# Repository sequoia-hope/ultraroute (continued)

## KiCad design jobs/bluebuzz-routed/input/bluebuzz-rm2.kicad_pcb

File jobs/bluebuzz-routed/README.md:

# bluebuzz-routed

bluebuzz fully routed by the MIT core router: **0 unconnected, 0 errors, no dangling copper** by
KiCad 9's DRC after a zone refill, under the board's own project rules (which make dangling
copper an error). Both USB pairs are routed as length-matched differential pairs (0.15 mm
tracks, 0.15 mm gap): USB_DP/USB_DM from the connector to the series resistors run side by side
for 76% and 72% of their length, 0.00 mm apart end to end (the hand-routed board: 31% side by
side); USB_DP_C/USB_DM_C, the 3.7 mm on from the resistors to the RP2350, run side by side on
F.Cu with no via for 58% and 60%, 0.13 mm apart (their pins are left out of the fan-out so the
pair reaches them straight). Stripped of all copper (the bluebuzz-kicad job), routed with
--strip-all --negotiate --rip-up --nudge --tighten --prefanout --diff-pairs --seed 2, 240 s on 1 thread (105.2 s used). No part moved. 265 vias and 1358
mm of track; the hand-finished board has 331 vias.

Command, on `jobs/bluebuzz-kicad/input/bluebuzz-rm2.kicad_pcb`:

    ultraroute route bluebuzz-rm2.kicad_pcb -o out.kicad_pcb --strip-all --negotiate --rip-up --nudge --tighten --prefanout --diff-pairs --seed 2 --timeout 240 --threads 1

The input here is that output after `tools/refill_zones.py`, so the pours show as KiCad fills
them. It is a finished board to look at, not a routing job: the studio loads it as it is. Lab
record: experiment `diffpairs-26`, run `BS-s2`; coupling and skew measured with
`cargo run --release -p grid --example pair_check`; see `docs/focus-trapped-escapes.md`.

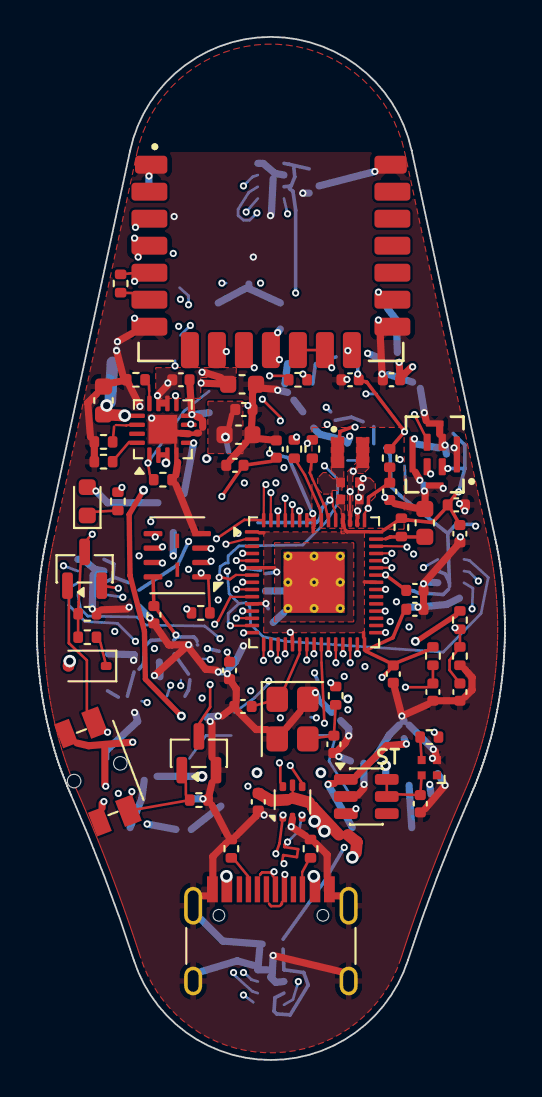
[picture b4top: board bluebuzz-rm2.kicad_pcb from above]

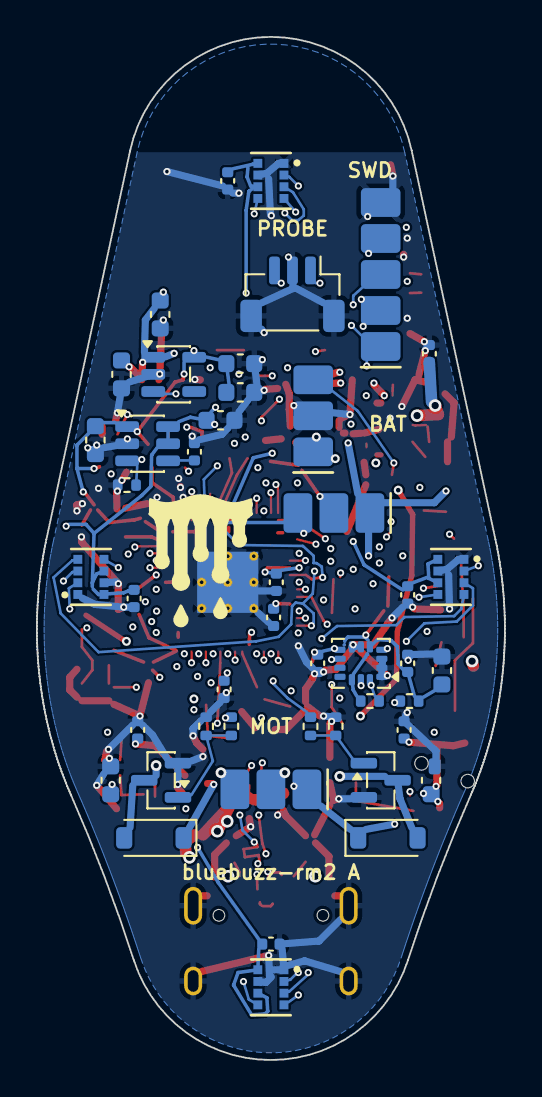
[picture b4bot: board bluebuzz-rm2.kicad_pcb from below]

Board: 6 copper layers, 26.0 x 56.8 mm, 109 parts (45 on the bottom side), 72 nets.

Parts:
C2, C13, C14, C15, C41, C43, C64, C82, C88, C89, C91, C92, C93, C94, C95, C96, C97, C98, C101, C102, C120, C121, C122, C123, C130, C132, C133, C140: 100n; C_0402_1005Metric
C10, C11, C12, C22, C52, C100, C131: 10u; C_0603_1608Metric
C20, C21, C51, C85: 1u; C_0603_1608Metric
C40, C42: 22u; C_0603_1608Metric
C50: 470p; C_0402_1005Metric
C80, C83: 4.7u; C_0402_1005Metric_small_pads
C81, C84: 4.7u; C_0402_1005Metric
C86, C87: 15p; C_0402_1005Metric
D1: CHG; LED_0603_1608Metric
D2: XL-1010RGBC; LED_1010_WS2812
D3, D4: B5819W; D_SOD-123
D5: BAT54C; SOT-23
D6: 1N4148WS; D_SOD-323
J1: USB-C; USB_C_Receptacle_HRO_TYPE-C-31-M-12
J2: BAT; PadRow_3x_solder
J3: SWD; PadRow_5x_pogo
J4: MOT; PadRow_3x_solder
J5: TP; PadRow_3x_pogo
J6: PROBE; JST_SH_BM03B-SRSS-TB_1x03-1MP_P1.00mm_Vertical
L1: 3.3u; L_pol_2016
Q1, Q2: AO3400A; SOT-23
Q3: 2N7002; SOT-23
R1, R2: 5.1k; R_0402_1005Metric
R3, R4: 27R; R_0402_1005Metric
R10: 1.78k; R_0402_1005Metric
R11: 1.62k; R_0402_1005Metric
R12: 45.3k; R_0402_1005Metric
R13, R81, R88: 10k; R_0402_1005Metric
R14, R62: 330R; R_0402_1005Metric
R40, R42: 100R; R_0402_1005Metric
R41, R43, R130, R131: 4.7k; R_0402_1005Metric
R50, R63, R64, R66: 100k; R_0402_1005Metric
R60, R61: 1M; R_0402_1005Metric
R80: 470R; R_0402_1005Metric
R84: 33R; R_0402_1005Metric
R85: 10R; R_0402_1005Metric
R86, R87: 1k; R_0402_1005Metric
SW1: PWR; Panasonic_EVQPUL_EVQPUC
U1: RP2350A; QFN-60-1EP_7x7mm_P0.4mm_EP3.4x3.4mm_ThermalVias
U2: BQ24074RGT; VQFN-16-1EP_3x3mm_P0.5mm_EP1.6x1.6mm
U3: TLV75533PDBV; SOT-23-5
U5, U11: TPS22918DBVR; SOT-23-6
U6: W25Q32JVUUIQ; Winbond_USON-8-2EP_3x4mm_P0.8mm_EP0.2x0.8mm
U7: RM2
U10: USBLC6-2P6; SOT-666
U20, U21, U22, U23: DPS368; DPS368_LGA-8
U30: LSM6DS3TR-C; LGA-14_3x2.5mm_P0.5mm_LayoutBorder3x4y
U40: MP34DT05-A; MP34DT05_HCLGA-4
Y1: 12MHz; Crystal_SMD_3225-4Pin_3.2x2.5mm

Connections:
1V1: C80.1, C81.1, C82.1, C98.1, J5.3, L1.1, U1.6, U1.23, U1.39, U1.50
3V3A: C85.1, R85.2, U1.44
3V3_SENS: C52.1, C120.1, C121.1, C122.1, C123.1, U5.5, U5.6, U20.6, U20.8, U21.6, U21.8, U22.6, U22.8, U23.6, U23.8
3V3_SYS: C21.1, C22.1, C51.1, C83.1, C88.1, C91.1, C92.1, C93.1, C94.1, C95.1, C96.1, C97.1, C102.1, C130.1, C131.1, C132.1, C140.1, J5.2, R84.1, R85.1, R88.1, R130.1, R131.1, U1.1, U1.11, U1.20, U1.30, U1.38, U1.45, U1.49, U1.53, U1.54, U3.5, U5.1, U6.8, U7.14, U11.3, U30.5, U30.8, U30.12, U40.1
BOOTSEL: J3.4, R87.2
BTN: Q3.3, U1.12
BTN_RAW: D5.1, Q3.1, R64.1, SW1.2
CC1: J1.A5, R1.1
CC2: J1.B5, R2.1
CHG_LED: D1.1, R14.1
CHG_N: R14.2, U2.9
CT_SENS: C50.1, U5.4
GND: C2.2, C10.2, C11.2, C12.2, C13.2, C14.2, C15.2, C20.2, C21.2, C22.2, C40.2, C41.2, C42.2, C43.2, C50.2, C51.2, C52.2, C64.2, C80.2, C81.2, C82.2, C83.2, C84.2, C85.2, C86.2, C87.2, C88.2, C89.2, C91.2, C92.2, C93.2, C94.2, C95.2, C96.2, C97.2, C98.2, C100.2, C101.2, C102.2, C120.2, C121.2, C122.2, C123.2, C130.2, C131.2, C132.2, C133.2, C140.2, D2.3, J1.A1, J1.A12, J1.B1, J1.B12, J1.S1, J2.2, J3.5, J6.2, J6.MP, Q1.2, Q2.2, Q3.2, R1.2, R2.2, R10.2, R11.2, R12.2, R13.2, R41.2, R43.2, R50.2, R61.2, R63.2, R64.2, U1.47, U1.61, U2.4, U2.6, U2.8, U2.17, U3.2, U5.2, U6.4, U7.1, U7.4, U7.7, U7.11, U7.15, U7.21, U10.2, U11.2, U20.1, U20.7, U21.1, U21.7, U22.1, U22.7, U23.1, U23.7, U30.1, U30.2, U30.3, U30.6, U30.7, U40.2, U40.5, Y1.2, Y1.4
ILIM: R11.1, U2.12
IMU_INT1: U1.8, U30.4
IMU_INT2: U1.29, U30.9
ISET: R10.1, U2.16
LDO_EN: D5.3, R63.1, R66.2, U3.3
LED_DIN: D2.4, R62.2
LED_STAT: R62.1, U1.34
LED_VDD: C133.1, D2.2, U11.5, U11.6
MOTOR1_G: Q1.1, R40.2, R41.1
MOTOR1_PWM: R40.1, U1.17
MOTOR1_SW: D3.2, J4.2, Q1.3
MOTOR2_G: Q2.1, R42.2, R43.1
MOTOR2_PWM: R42.1, U1.28
MOTOR2_SW: D4.2, J4.3, Q2.3
PDM_CLK: U1.43, U40.3
PDM_DATA: U1.42, U40.4
PG_N: U1.13, U2.7
PWR_HOLD: D5.2, U1.31
QSPI_SCLK: U1.56, U6.6
QSPI_SD0: U1.57, U6.5
QSPI_SD1: U1.59, U6.2
QSPI_SD2: U1.58, U6.3
QSPI_SD3: U1.55, U6.7
QSPI_SS: R87.1, U1.60, U6.1
RUN: C89.1, J3.3, R88.2, U1.26
SCL: R131.2, U1.10, U30.13
SDA: R130.2, U1.9, U30.14
SENS_EN: R50.1, U1.7, U5.3
SWCLK: J3.2, J6.1, U1.24
SWDIO: J3.1, J6.3, U1.25
TAC_CS1: U1.2, U20.2
TAC_CS2: U1.18, U21.2
TAC_CS3: U1.19, U22.2
TAC_CS4: U1.27, U23.2
TAC_SCK: U1.14, U20.4, U21.4, U22.4, U23.4
TAC_SDI: U1.15, U20.3, U21.3, U22.3, U23.3
TAC_SDO: U1.16, U20.5, U21.5, U22.5, U23.5
TMR: R12.1, U2.14
TS: J2.3, R13.1, U2.1
USB_DM: J1.A7, J1.B7, R4.1, U10.3, U10.4
USB_DM_C: R4.2, U1.51
USB_DP: J1.A6, J1.B6, R3.1, U10.1, U10.6
USB_DP_C: R3.2, U1.52
VBAT: C12.1, C15.1, J2.1, R60.1, U2.2, U2.3
VBAT_SENSE: C64.1, R60.2, R61.1, U1.40
VBUS: C2.1, C10.1, C13.1, D6.2, J1.A4, J1.A9, J1.B4, J1.B9, U2.13, U10.5
VBUS_EN: D6.1, R66.1
VREG_AVDD: C84.1, R84.2, U1.46
VREG_LX: L1.2, U1.48
VSYS: C11.1, C14.1, C20.1, C40.1, C41.1, C42.1, C43.1, C100.1, C101.1, D1.2, D3.1, D4.1, J4.1, J5.1, SW1.1, U2.5, U2.10, U2.11, U3.1, U7.16, U11.1
WL_CLK: U1.5, U7.3
WL_CS: U1.37, U7.9
WL_DATA: R80.2, R81.2, U1.4, U7.5
WL_DOUT: R80.1, U7.6
WL_IRQ: R81.1, U7.10
WL_ON: U1.41, U7.12, U7.13
XIN: C86.1, U1.21, Y1.1
XOUT: R86.1, U1.22
XTAL2: C87.1, R86.2, Y1.3

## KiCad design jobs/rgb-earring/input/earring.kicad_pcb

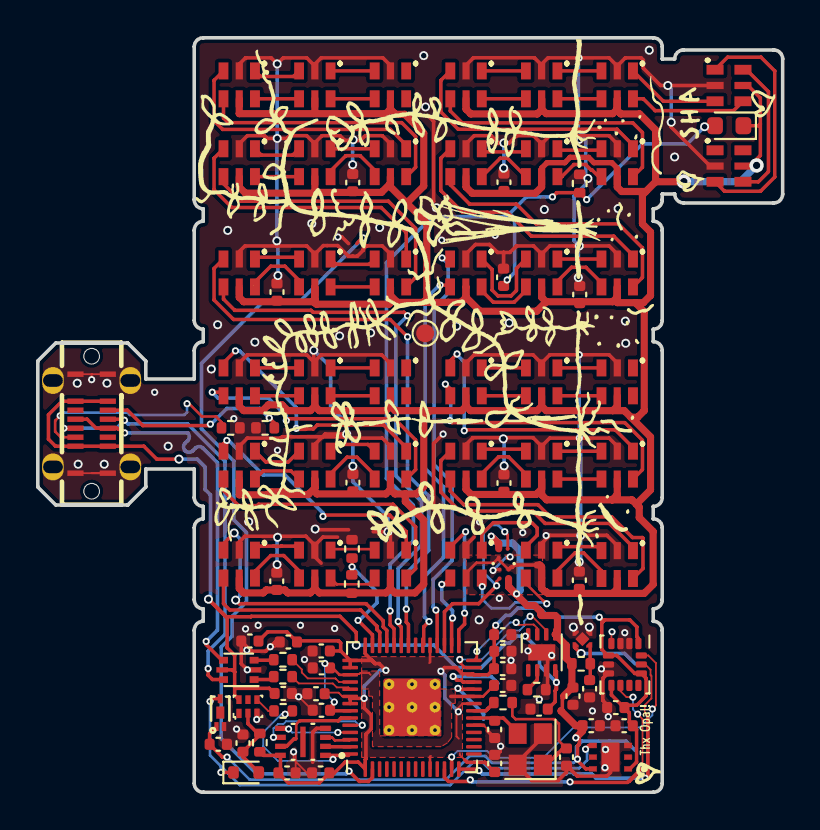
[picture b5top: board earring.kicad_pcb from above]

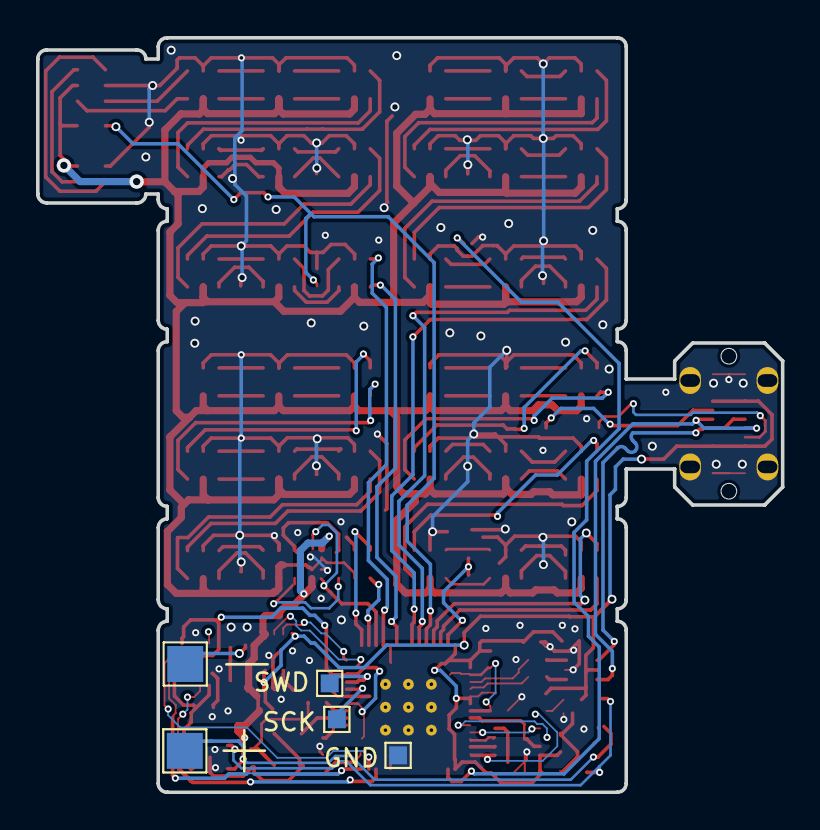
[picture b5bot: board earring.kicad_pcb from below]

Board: 2 copper layers, 41.4 x 41.9 mm, 104 parts (5 on the bottom side), 115 nets.

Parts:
C1, C4, C8, C9, C11, C13, C14, C15, C16, C17, C18, C19, C22, C23, C24: 100n; C_0402_1005Metric
C2, C3, C7, C21: 10u; C_0402_1005Metric
C5, C6: 20p; C_0402_1005Metric
C10, C12, C20, C25, C26, C27, C28, C29, C30, C31, C32, C33: 1u; C_0402_1005Metric
D2: D; D_SOD-523
J2: USB_C_Receptacle_USB2.0; USB-C-TH_GT-USB-7055
Q5: light_sensor; LED_0603_1608Metric
R1, R5: 1.1k; R_0402_1005Metric
R2, R12: 100k; R_0402_1005Metric
R3, R4, R8: 5.1k; R_0402_1005Metric
R6, R7: 27; R_0402_1005Metric
R9: 510; R_0402_1005Metric
R10: 10k; R_0402_1005Metric
R11: 40.2k; R_0402_1005Metric
TP1: TestPoint; TestPoint_Pad_D1.0mm
TP2, TP3: TestPoint; TestPoint_Pad_2.0x2.0mm
TP4, TP5, TP6: TestPoint; TestPoint_Pad_1.0x1.0mm
U1: Magnetic Switch; DFN1608-3_L1.5-W0.8-P0.42-BL-EP
U3: RP2040; RP2040-QFN-56
U4: W25Q16JVUXIQ; IC_W25Q16JVUXIQ_TR
U5, U11, U12, U13, U14, U15, U16, U17, U18, U19, U21, U22, U25, U26, U27, U28, U29, U30, U31, U32, U33, U34, U35, U36, U37, U38, U39, U40, U41, U42, U45, U46, U47, U48, U49, U50, U52: LED-SK9822-EC20
U6: Buffer; UFDFN-6_1.45x1mm
U7: LSM6DS3; LGA-14_3x2.5mm_P0.5mm_LayoutBorder3x4y
U8: DS6091AED4; DFN1x1
U9: NCP730BMT330TBG; WDFN-6-2x2
U10: USBLC6-2P6; SOT-666
U20: LGS4056H; DFN-8-1EP_2x2mm_P0.5mm_EP0.9x1.5mm
U24: SK9822-EC20; LED-SK9822-EC20
U43, U44: TPS22913BYZVR; YZV0004ADAD
Y1: Crystal_GND24; Crystal_SMD_2520-4Pin_2.5x2.0mm

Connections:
+1V1: C8.1, C9.1, C10.1, U3.23 (DVDD), U3.45 (VREG_VOUT), U3.50 (DVDD)
+3V3: C1.1, C7.1, C11.1, C12.1, C13.1, C14.1, C15.1, C16.1, C17.1, C18.1, C20.1, C23.1, R2.1, U3.1 (IOVDD), U3.10 (IOVDD), U3.22 (IOVDD), U3.26 (RUN), U3.33 (IOVDD), U3.42 (IOVDD), U3.43 (ADC_AVDD), U3.44 (VREG_IN), U3.48 (USB_VDD), U3.49 (IOVDD), U4.8 (VCC), U7.1 (SDO/SA0), U7.5 (VDDIO), U7.8 (VDD), U7.12 (CS), U9.1 (OUT)
+BATT: C2.1, C19.1, C21.1, R9.2, TP3.1, U1.1 (VCC), U9.6 (IN), U20.5 (BAT), U43.A2 (VIN), U44.A2 (VIN)
/3v3EN: D2.1 (K), U1.2 (VOUT), U9.4 (EN)
/BATT_SENSE: R11.1, R12.2, U3.41 (GPIO29_ADC3)
/CHRG: U3.27 (GPIO16), U20.6 (Done)
/DONE: U3.28 (GPIO17), U20.7 (CHRG)
/LED_1_V: C25.1, C26.1, C27.1, C28.1, C29.1, C30.1, C31.1, C32.1, Q5.1, R11.2, U5.5 (VDD), U11.5 (VDD), U12.5 (VDD), U13.5 (VDD), U14.5 (VDD), U15.5 (VDD), U16.5 (VDD), U17.5 (VDD), U18.5 (VDD), U19.5 (VDD), U21.5 (VDD), U22.5 (VDD), U24.5 (VDD), U25.5 (VDD), U26.5 (VDD), U27.5 (VDD), U28.5 (VDD), U29.5 (VDD), U30.5 (VDD), U31.5 (VDD), U32.5 (VDD), U33.5 (VDD), U34.5 (VDD), U35.5 (VDD), U36.5 (VDD), U37.5 (VDD), U38.5 (VDD), U39.5 (VDD), U40.5 (VDD), U41.5 (VDD), U42.5 (VDD), U43.A1 (VOUT), U44.A1 (VOUT), U45.5 (VDD), U46.5 (VDD), U47.5 (VDD), U48.5 (VDD), U49.5 (VDD), U50.5 (VDD), U52.5 (VDD)
/LED_SCK_1: U3.30 (GPIO19), U48.4 (CKL)
/LED_SCK_2: U3.34 (GPIO22), U41.4 (CKL)
/LED_SCK_3: U3.37 (GPIO25), U38.4 (CKL)
/LED_SCK_4: U3.40 (GPIO28_ADC2), U45.4 (CKL)
/LED_TX_1: U3.29 (GPIO18), U48.3 (SDI)
/LED_TX_2: U3.32 (GPIO21), U41.3 (SDI)
/LED_TX_3: U3.36 (GPIO24), U38.3 (SDI)
/LED_TX_4: U3.39 (GPIO27_ADC1), U45.3 (SDI)
/LIGHT_SENSE: C33.1, Q5.2, R8.1, U3.38 (GPIO26_ADC0)
/QSPI_SCLK: U3.52 (QSPI_SCLK), U4.6 (CLK)
/QSPI_SD0: U3.53 (QSPI_SD0), U4.5 (DI_(IO0))
/QSPI_SD1: U3.55 (QSPI_SD1), U4.2 (DO_(IO1))
/QSPI_SD2: U3.54 (QSPI_SD2), U4.3 (~WP_(IO2))
/QSPI_SD3: U3.51 (QSPI_SD3), U4.7 (~HOLD_(IO3))
/QSPI_SS: R1.1, U3.56 (QSPI_SS), U4.1 (~{CS)
/SW_LED_1: U3.31 (GPIO20), U43.B2 (ON), U44.B2 (ON)
/USB_D1+: R6.1, U10.1 (I/O1)
/USB_D1-: R7.1, U10.3 (I/O2)
/USB_D+: J2.A6 (D+), J2.B6 (D+), U10.6 (I/O1)
/USB_D-: J2.A7 (D-), J2.B7 (D-), U10.4 (I/O2)
/USB_DN: R7.2, U3.46 (USB_DM)
/USB_DP: R6.2, U3.47 (USB_DP)
/XIN: C5.1, U3.20 (XIN), Y1.3
/XOUT: R5.1, U3.21 (XOUT)
/~USB_BOOT: R1.2, U6.4
BAT-: TP2.1, U8.4 (EB-)
GND: C1.2, C2.2, C3.2, C4.2, C5.2, C6.2, C7.2, C8.2, C9.2, C10.2, C11.2, C12.2, C13.2, C14.2, C15.2, C16.2, C17.2, C18.2, C19.2, C20.2, C21.2, C22.2, C23.2, C24.2, C25.2, C26.2, C27.2, C28.2, C29.2, C30.2, C31.2, C32.2, C33.2, J2.A1 (GND), J2.A12 (GND), J2.B1 (GND), J2.B12 (GND), J2.S1 (SHIELD), R3.1, R4.2, R8.2, R10.1, R12.1, TP1.1, TP6.1, U1.3 (GND), U3.19 (TESTEN), U3.57 (GND), U4.4 (GND), U5.2 (GND), U6.3 (GND), U7.2 (SDX), U7.3 (SCX), U7.6 (GND), U7.7 (GND), U8.2 (VSS), U8.3 (VSS), U8.5 (VSS), U9.3 (GND), U9.EP (EPAD), U10.2 (GND), U11.2 (GND), U12.2 (GND), U13.2 (GND), U14.2 (GND), U15.2 (GND), U16.2 (GND), U17.2 (GND), U18.2 (GND), U19.2 (GND), U20.3 (GND), U20.9 (PAD), U21.2 (GND), U22.2 (GND), U24.2 (GND), U25.2 (GND), U26.2 (GND), U27.2 (GND), U28.2 (GND), U29.2 (GND), U30.2 (GND), U31.2 (GND), U32.2 (GND), U33.2 (GND), U34.2 (GND), U35.2 (GND), U36.2 (GND), U37.2 (GND), U38.2 (GND), U39.2 (GND), U40.2 (GND), U41.2 (GND), U42.2 (GND), U43.B1 (GND), U44.B1 (GND), U45.2 (GND), U46.2 (GND), U47.2 (GND), U48.2 (GND), U49.2 (GND), U50.2 (GND), U52.2 (GND), Y1.2, Y1.4
INT: U3.12 (GPIO9), U7.9 (INT2)
unnamed: C6.1, R5.2, Y1.1
unnamed: C3.1, D2.2 (A), R2.2, U6.2
unnamed: J2.A5 (CC1), R3.2
unnamed: J2.B5 (CC2), R4.1
unnamed: C22.1, R9.1, U8.1 (BAT)
unnamed: U5.6 (CKO), U11.4 (CKL)
unnamed: U11.6 (CKO), U12.4 (CKL)
unnamed: U5.1 (SDO), U11.3 (SDI)
unnamed: U11.1 (SDO), U12.3 (SDI)
unnamed: U13.4 (CKL), U47.6 (CKO)
unnamed: U13.6 (CKO), U14.4 (CKL)
unnamed: U13.3 (SDI), U47.1 (SDO)
unnamed: U13.1 (SDO), U14.3 (SDI)
unnamed: U14.6 (CKO), U15.4 (CKL)
unnamed: U14.1 (SDO), U15.3 (SDI)
unnamed: U5.4 (CKL), U15.6 (CKO)
unnamed: U5.3 (SDI), U15.1 (SDO)
unnamed: U16.4 (CKL), U22.6 (CKO)
unnamed: U16.6 (CKO), U17.4 (CKL)
unnamed: U16.3 (SDI), U22.1 (SDO)
unnamed: U16.1 (SDO), U17.3 (SDI)
unnamed: U17.6 (CKO), U18.4 (CKL)
unnamed: U17.1 (SDO), U18.3 (SDI)
unnamed: U19.4 (CKL), U52.6 (CKO)
unnamed: U19.6 (CKO), U21.4 (CKL)
unnamed: U19.3 (SDI), U52.1 (SDO)
unnamed: U19.1 (SDO), U21.3 (SDI)
unnamed: R10.2, U20.2 (Prog)
unnamed: U21.6 (CKO), U22.4 (CKL)
unnamed: U21.1 (SDO), U22.3 (SDI)
unnamed: U24.4 (CKL), U33.6 (CKO)
unnamed: U24.6 (CKO), U25.4 (CKL)
unnamed: U24.3 (SDI), U33.1 (SDO)
unnamed: U24.1 (SDO), U25.3 (SDI)
unnamed: U25.6 (CKO), U26.4 (CKL)
unnamed: U25.1 (SDO), U26.3 (SDI)
unnamed: U27.4 (CKL), U36.6 (CKO)
unnamed: U27.6 (CKO), U28.4 (CKL)
unnamed: U27.3 (SDI), U36.1 (SDO)
unnamed: U27.1 (SDO), U28.3 (SDI)
unnamed: U28.6 (CKO), U29.4 (CKL)
unnamed: U28.1 (SDO), U29.3 (SDI)
unnamed: U29.6 (CKO), U30.4 (CKL)
unnamed: U29.1 (SDO), U30.3 (SDI)
unnamed: U30.6 (CKO), U37.4 (CKL)
unnamed: U30.1 (SDO), U37.3 (SDI)
unnamed: U31.4 (CKL), U40.6 (CKO)
unnamed: U31.6 (CKO), U32.4 (CKL)
unnamed: U31.3 (SDI), U40.1 (SDO)
unnamed: U31.1 (SDO), U32.3 (SDI)
unnamed: U32.6 (CKO), U33.4 (CKL)
unnamed: U32.1 (SDO), U33.3 (SDI)
unnamed: U34.4 (CKL), U50.6 (CKO)
unnamed: U34.6 (CKO), U35.4 (CKL)
unnamed: U34.3 (SDI), U50.1 (SDO)
unnamed: U34.1 (SDO), U35.3 (SDI)
unnamed: U35.6 (CKO), U36.4 (CKL)
unnamed: U35.1 (SDO), U36.3 (SDI)
unnamed: U38.6 (CKO), U39.4 (CKL)
unnamed: U38.1 (SDO), U39.3 (SDI)
unnamed: U39.6 (CKO), U40.4 (CKL)
unnamed: U39.1 (SDO), U40.3 (SDI)
unnamed: U41.6 (CKO), U42.4 (CKL)
unnamed: U41.1 (SDO), U42.3 (SDI)
unnamed: U42.6 (CKO), U50.4 (CKL)
unnamed: U42.1 (SDO), U50.3 (SDI)
unnamed: U45.6 (CKO), U46.4 (CKL)
unnamed: U45.1 (SDO), U46.3 (SDI)
unnamed: U46.6 (CKO), U47.4 (CKL)
unnamed: U46.1 (SDO), U47.3 (SDI)
unnamed: U48.6 (CKO), U49.4 (CKL)
unnamed: U48.1 (SDO), U49.3 (SDI)
unnamed: U49.6 (CKO), U52.4 (CKL)
unnamed: U49.1 (SDO), U52.3 (SDI)
SCL: U3.14 (GPIO11), U7.13 (SCL)
SDA: U3.13 (GPIO10), U7.14 (SDA)
SWCLK: TP4.1, U3.24 (SWCLK)
SWD: TP5.1, U3.25 (SWD)
VBUS: C4.1, C24.1, J2.A4 (VBUS), J2.A9 (VBUS), J2.B4 (VBUS), J2.B9 (VBUS), U6.6 (VCC), U10.5 (VBUS), U20.4 (VCC), U20.8 (CE)
